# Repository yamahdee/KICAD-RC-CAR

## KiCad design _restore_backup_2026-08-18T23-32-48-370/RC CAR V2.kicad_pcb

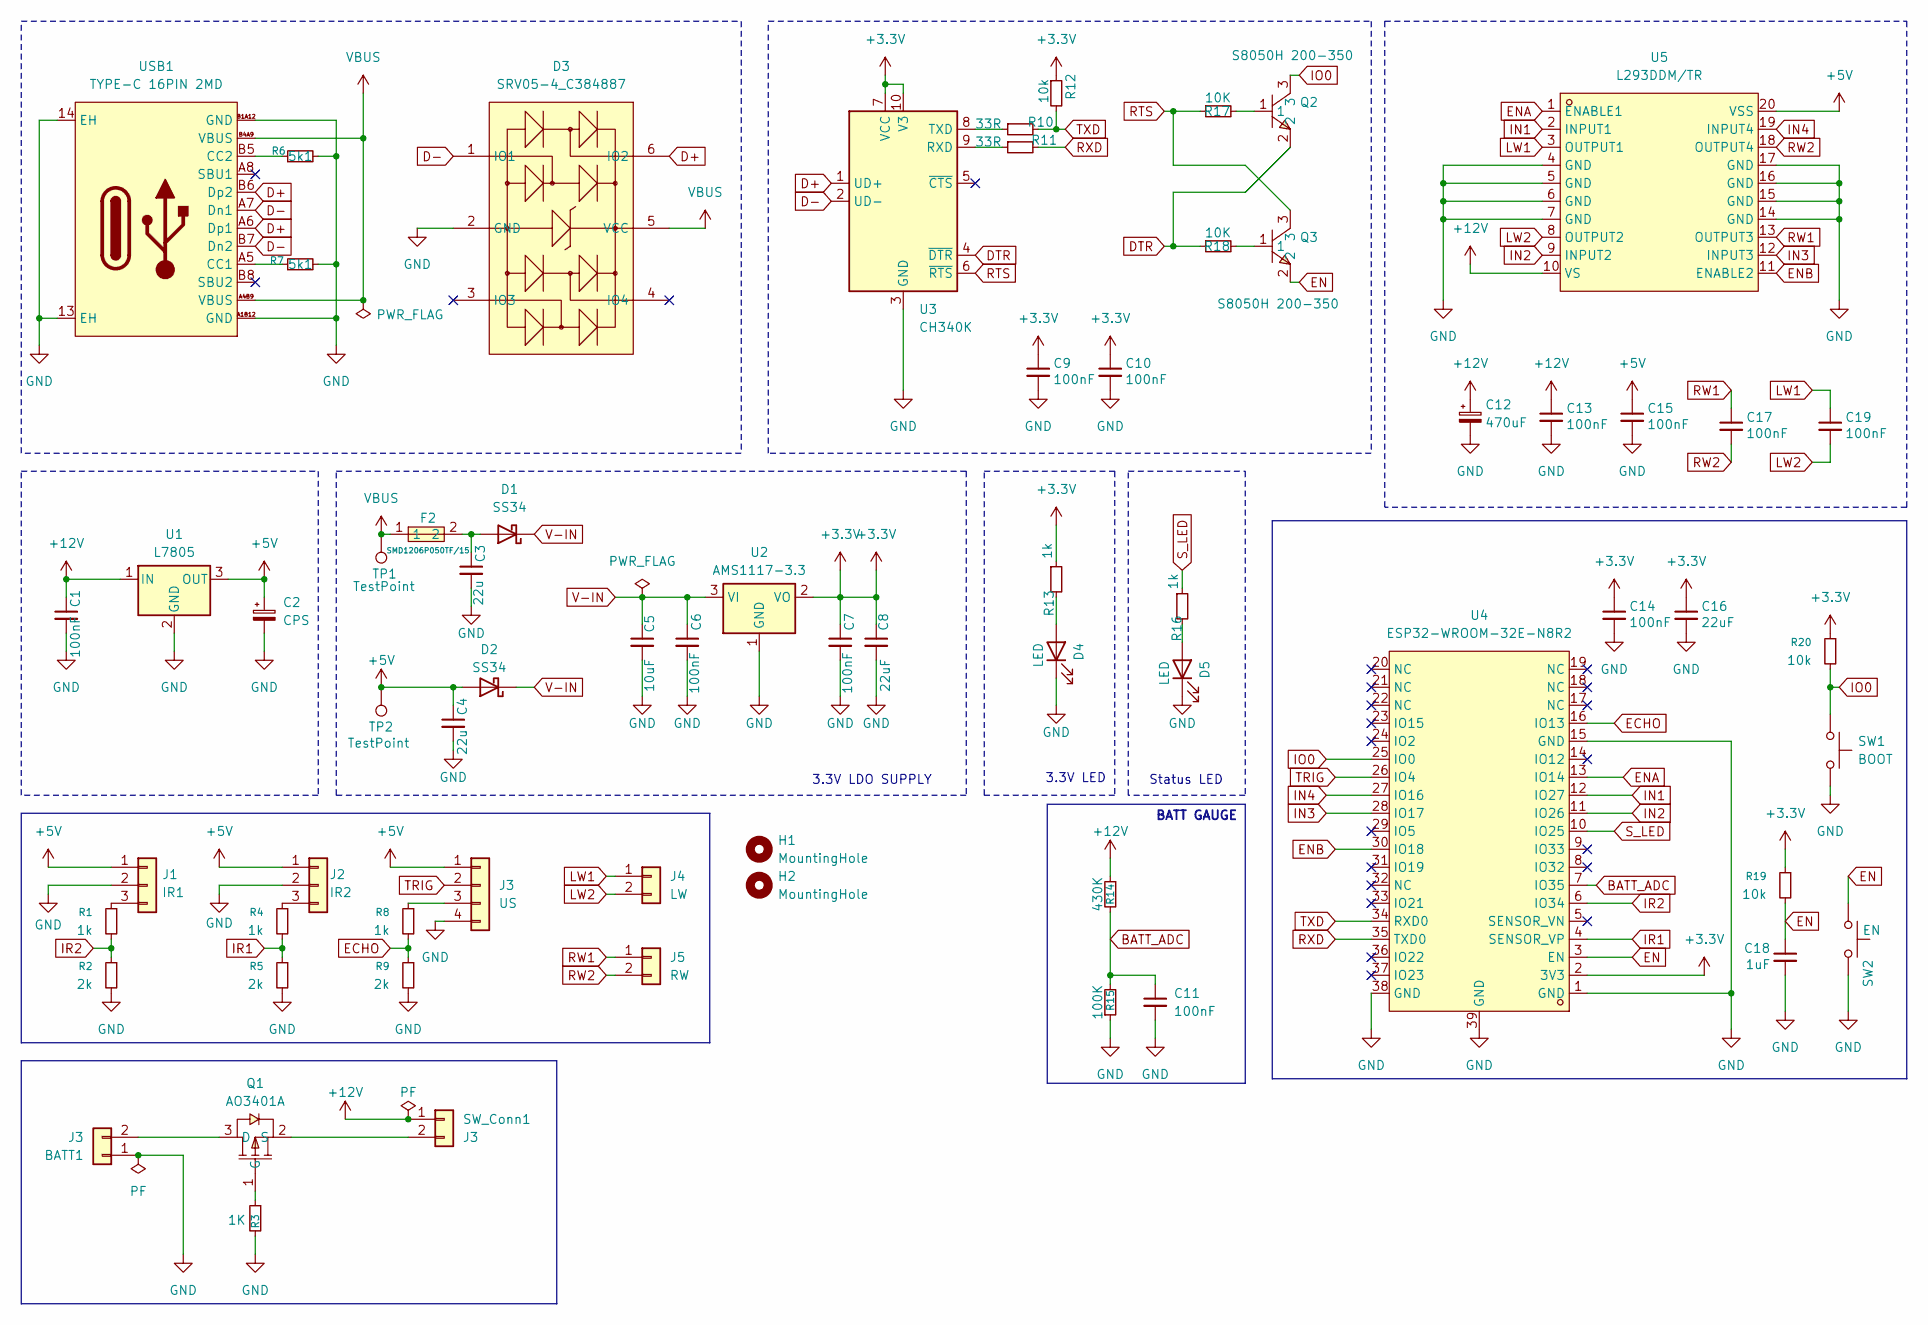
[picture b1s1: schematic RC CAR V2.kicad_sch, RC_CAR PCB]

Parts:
BATT1: J3; JST_XH_B2B-XH-AM_1x02_P2.50mm_Vertical
C1, C6, C7, C9, C10, C11, C13, C14, C15, C17, C19: 100nF; C_0805_2012Metric_Pad1.18x1.45mm_HandSolder
C2: CPS; CP_Radial_D5.0mm_P2.50mm
C3, C4: 22u; C_0805_2012Metric_Pad1.18x1.45mm_HandSolder
C5: 10uF; C_0805_2012Metric_Pad1.18x1.45mm_HandSolder
C8, C16: 22uF; C_0805_2012Metric_Pad1.18x1.45mm_HandSolder
C12: 470uF; CP_Radial_D8.0mm_P3.50mm
C18: 1uF; C_0805_2012Metric_Pad1.18x1.45mm_HandSolder
D1, D2: SS34; D_SMA_Handsoldering
D3: SRV05-4_C384887; SOT-23-6_L2.9-W1.6-P0.95-LS2.8-BR; MPN SRV05-4; LCSC Part C384887
D4, D5: LED; LED_0805_2012Metric_Pad1.15x1.40mm_HandSolder
F2: SMD1206P050TF/15; F1206; MPN SMD1206P050TF/15; LCSC Part C106264
H1, H2: MountingHole; MountingHole_2.1mm
J1: IR1; JST_XH_B3B-XH-AM_1x03_P2.50mm_Vertical
J2: IR2; JST_XH_B3B-XH-AM_1x03_P2.50mm_Vertical
J3: US; PinHeader_1x04_P2.54mm_Vertical
J4: LW; JST_XH_B2B-XH-AM_1x02_P2.50mm_Vertical
J5: RW; JST_XH_B2B-XH-AM_1x02_P2.50mm_Vertical
Q1: AO3401A; SOT-23_L2.9-W1.3-P1.90-LS2.4-BR; MPN AO3401A; LCSC Part C15127
Q2, Q3: S8050H 200-350; SOT-23-3_L2.9-W1.6-P1.90-LS2.8-BR; MPN S8050; LCSC Part C111272
R1, R4, R8, R13, R16: 1k; R_0805_2012Metric_Pad1.20x1.40mm_HandSolder
R2, R5, R9: 2k; R_0805_2012Metric_Pad1.20x1.40mm_HandSolder
R3: 1K; R_0805_2012Metric_Pad1.20x1.40mm_HandSolder
R6, R7: 5k1; R_0805_2012Metric_Pad1.20x1.40mm_HandSolder
R10, R11: 33R; R_0805_2012Metric_Pad1.20x1.40mm_HandSolder
R12, R19, R20: 10k; R_0805_2012Metric_Pad1.20x1.40mm_HandSolder
R14: 430K; R_0805_2012Metric_Pad1.20x1.40mm_HandSolder
R15: 100K; R_0805_2012Metric_Pad1.20x1.40mm_HandSolder
R17, R18: 10K; R_0805_2012Metric_Pad1.20x1.40mm_HandSolder
SW1: BOOT; SW_Tactile_SPST_NO_Straight_CK_PTS636Sx25SMTRLFS
SW2: EN; SW_Tactile_SPST_NO_Straight_CK_PTS636Sx25SMTRLFS
SW_Conn1: J3; JST_XH_B2B-XH-AM_1x02_P2.50mm_Vertical
TP1, TP2: TestPoint; TestPoint_Pad_D1.0mm
U1: L7805; TO-263-3_TabPin2
U2: AMS1117-3.3; SOT-223-3_TabPin2
U3: CH340K; SSOP-10-1EP_3.9x4.9mm_P1mm_EP2.1x3.3mm
U4: ESP32-WROOM-32E-N8R2; WIFI-SMD_ESP32-WROOM-32E; MPN ESP32-WROOM-32E-N8R2; LCSC Part C5361945
U5: L293DDM/TR; SOP-20_L12.8-W7.5-P1.27-LS10.4-BL; MPN L293DDM/TR; LCSC Part C2973803
USB1: TYPE-C 16PIN 2MD; USB-C-SMD_TYPE-C-16PIN-2MD-073; MPN TYPE-C 16PIN 2MD(073); LCSC Part C2765186

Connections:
+3.3V: C7.1, C8.1, C9.1, C10.1, C14.1, C16.1, R12.1, R13.1, R19.1, R20.1, U2.2 (VO), U3.7 (VCC), U3.10 (V3), U4.2 (3V3)
+5V: C2.1, C4.1, C15.1, D2.2 (A), J1.1, J2.1, J3.1, TP2.1 (1_1), U1.3 (OUT), U5.20 (VSS)
+12V: C1.1, C12.1, C13.1, R14.1, SW_Conn1.1, U1.1 (IN), U5.10 (VS)
BATT_ADC: C11.1, R14.2, R15.2, U4.7 (IO35)
D+: D3.6 (IO2), U3.1 (UD+), USB1.A6 (Dp1), USB1.B6 (Dp2)
D-: D3.1 (IO1), U3.2 (UD-), USB1.A7 (Dn1), USB1.B7 (Dn2)
DTR: Q2.2, R18.1, U3.4 (~DTR)
ECHO: R8.2, R9.1, U4.16 (IO13)
EN: C18.1, Q3.2, R19.2, SW2.1, U4.3 (EN)
ENA: U4.13 (IO14), U5.1 (ENABLE1)
ENB: U4.30 (IO18), U5.11 (ENABLE2)
GND: BATT1.1, C1.2, C2.2, C3.2, C4.2, C5.2, C6.2, C7.2, C8.2, C9.2, C10.2, C11.2, C12.2, C13.2, C14.2, C15.2, C16.2, C18.2, D3.2 (GND), D4.1 (K), D5.1 (K), J1.2, J2.2, J3.4, R2.2, R3.2, R5.2, R6.2, R7.2, R9.2, R15.1, SW1.2, SW2.2, U1.2 (GND), U2.1 (GND), U3.3 (GND), U3.11 (GND), U4.1 (GND), U4.15 (GND), U4.38 (GND), U4.39 (GND), U5.4 (GND), U5.5 (GND), U5.6 (GND), U5.7 (GND), U5.14 (GND), U5.15 (GND), U5.16 (GND), U5.17 (GND), USB1.13 (EH), USB1.14 (EH), USB1.A1B12 (GND), USB1.B1A12 (GND)
IN1: U4.12 (IO27), U5.2 (INPUT1)
IN2: U4.11 (IO26), U5.9 (INPUT2)
IN3: U4.28 (IO17), U5.12 (INPUT3)
IN4: U4.27 (IO16), U5.19 (INPUT4)
IO0: Q2.3, R20.2, SW1.1, U4.25 (IO0)
IR1: R4.2, R5.1, U4.4 (SENSOR_VP)
IR2: R1.2, R2.1, U4.6 (IO34)
LW1: C19.1, J4.1, U5.3 (OUTPUT1)
LW2: C19.2, J4.2, U5.8 (OUTPUT2)
unnamed: BATT1.2, Q1.3 (D)
unnamed: C3.1, D1.2 (A), F2.2
unnamed: D4.2 (A), R13.2
unnamed: D5.2 (A), R16.2
unnamed: J1.3, R1.1
unnamed: J2.3, R4.1
unnamed: J3.3, R8.1
unnamed: Q1.1 (G), R3.1
unnamed: Q1.2 (S), SW_Conn1.2
unnamed: Q2.1, R17.2
unnamed: Q3.1, R18.2
unnamed: R11.1, U3.9 (RXD)
unnamed: R10.1, U3.8 (TXD)
unnamed: R7.1, USB1.A5 (CC1)
unnamed: R6.1, USB1.B5 (CC2)
RTS: Q3.3, R17.1, U3.6 (~RTS)
RW1: C17.1, J5.1, U5.13 (OUTPUT3)
RW2: C17.2, J5.2, U5.18 (OUTPUT4)
RXD: R11.2, U4.35 (TXD0)
S_LED: R16.1, U4.10 (IO25)
TRIG: J3.2, U4.26 (IO4)
TXD: R10.2, R12.2, U4.34 (RXD0)
V-IN: C5.1, C6.1, D1.1 (K), D2.1 (K), U2.3 (VI)
VBUS: D3.5 (VCC), F2.1, TP1.1 (1_1), USB1.A4B9 (VBUS), USB1.B4A9 (VBUS)

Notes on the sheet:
3.3V LED
Status LED
3.3V LDO SUPPLY
BATT GAUGE

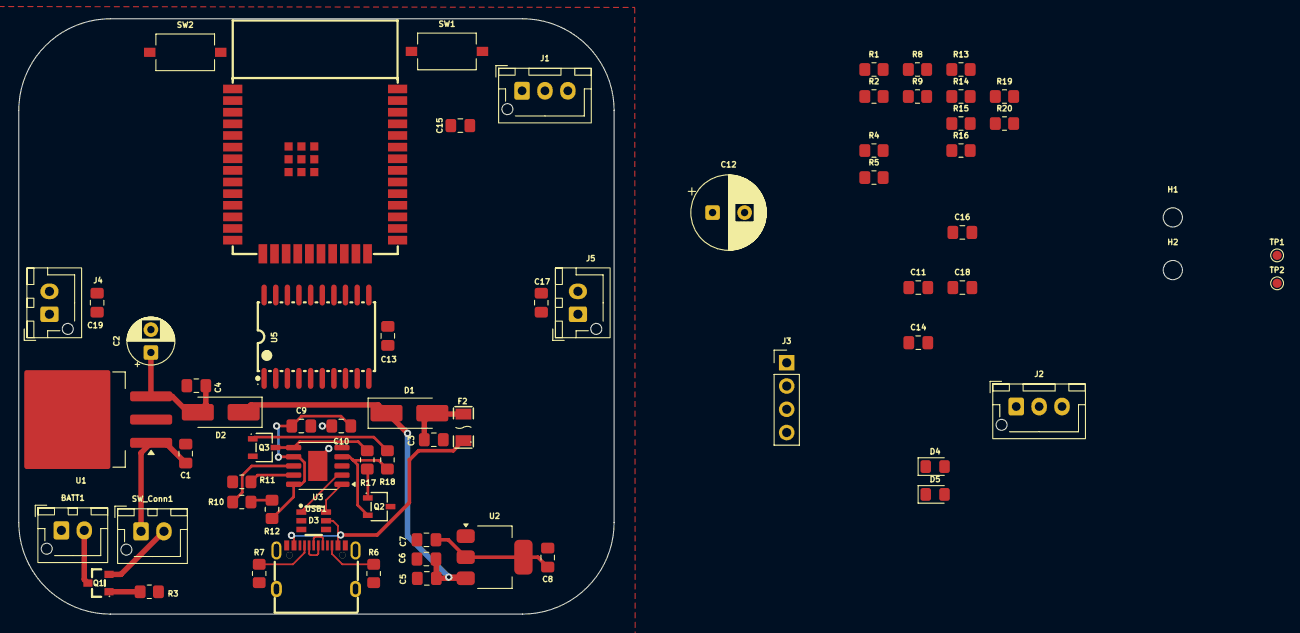
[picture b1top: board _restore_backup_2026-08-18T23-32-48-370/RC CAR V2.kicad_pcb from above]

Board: 2 copper layers, 65.0 x 65.0 mm, 67 parts (0 on the bottom side), 45 nets.

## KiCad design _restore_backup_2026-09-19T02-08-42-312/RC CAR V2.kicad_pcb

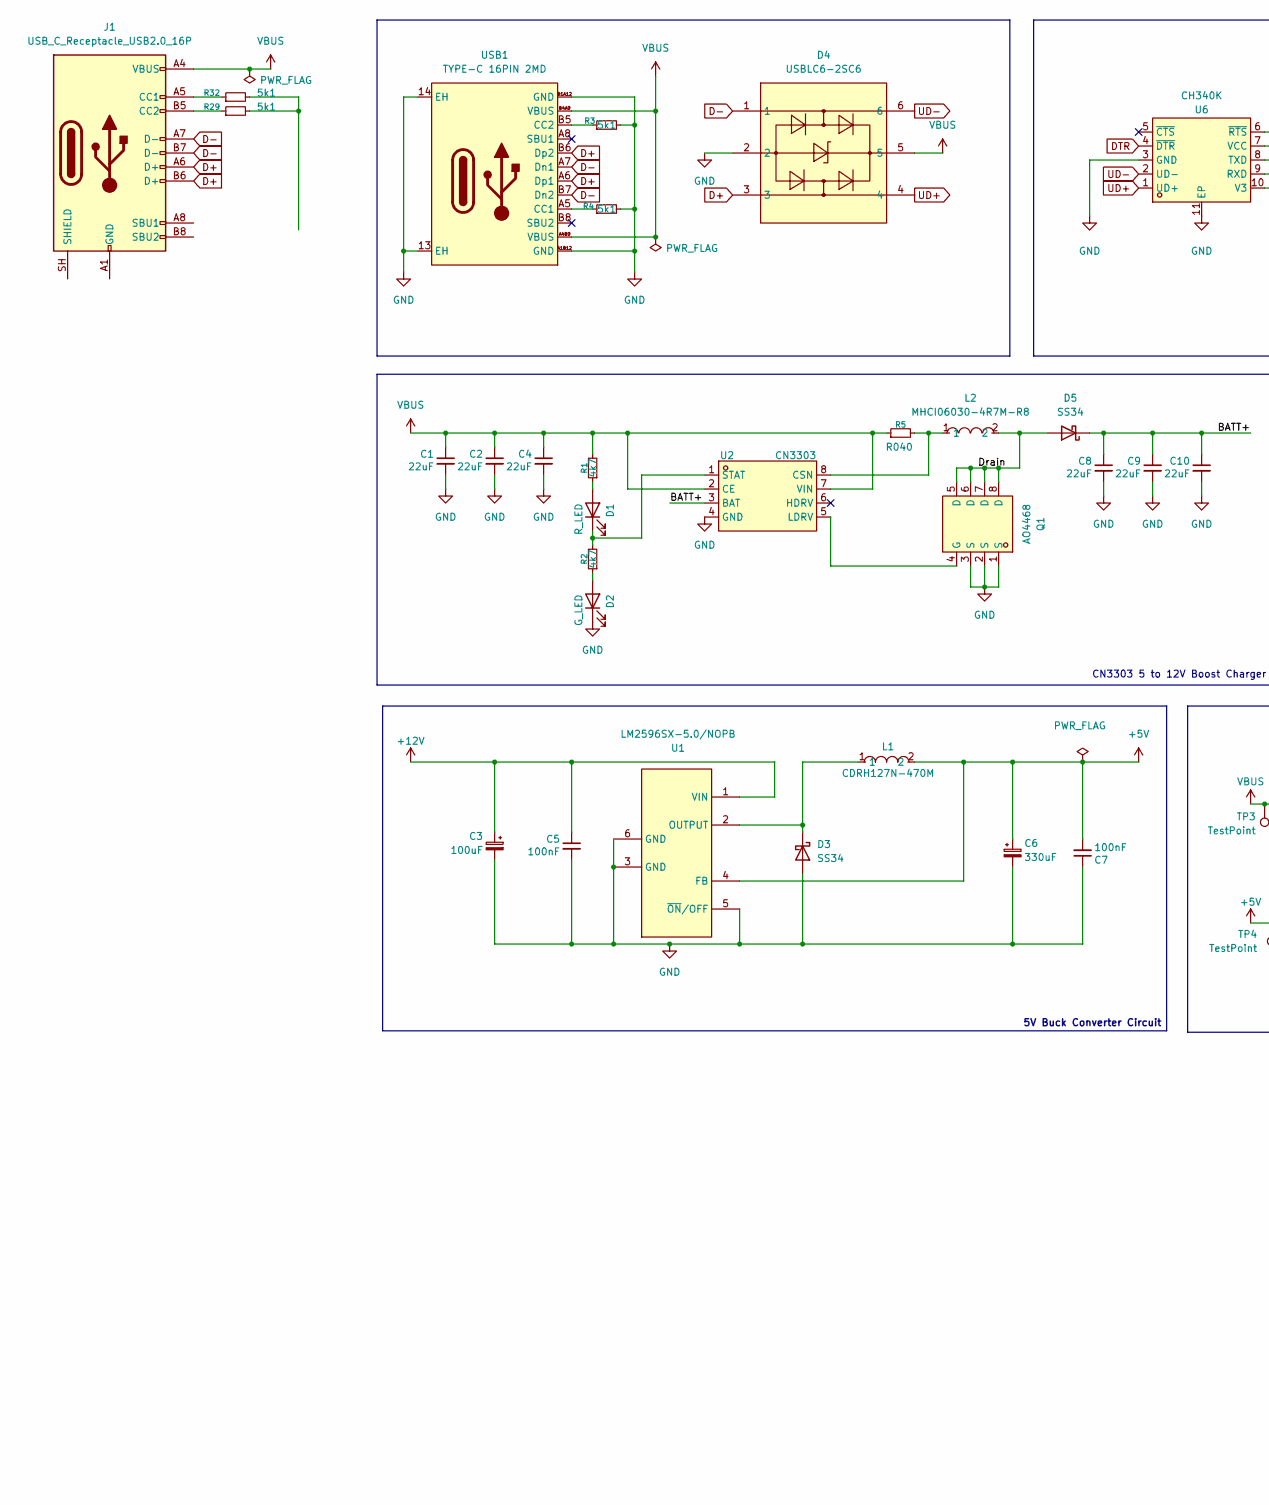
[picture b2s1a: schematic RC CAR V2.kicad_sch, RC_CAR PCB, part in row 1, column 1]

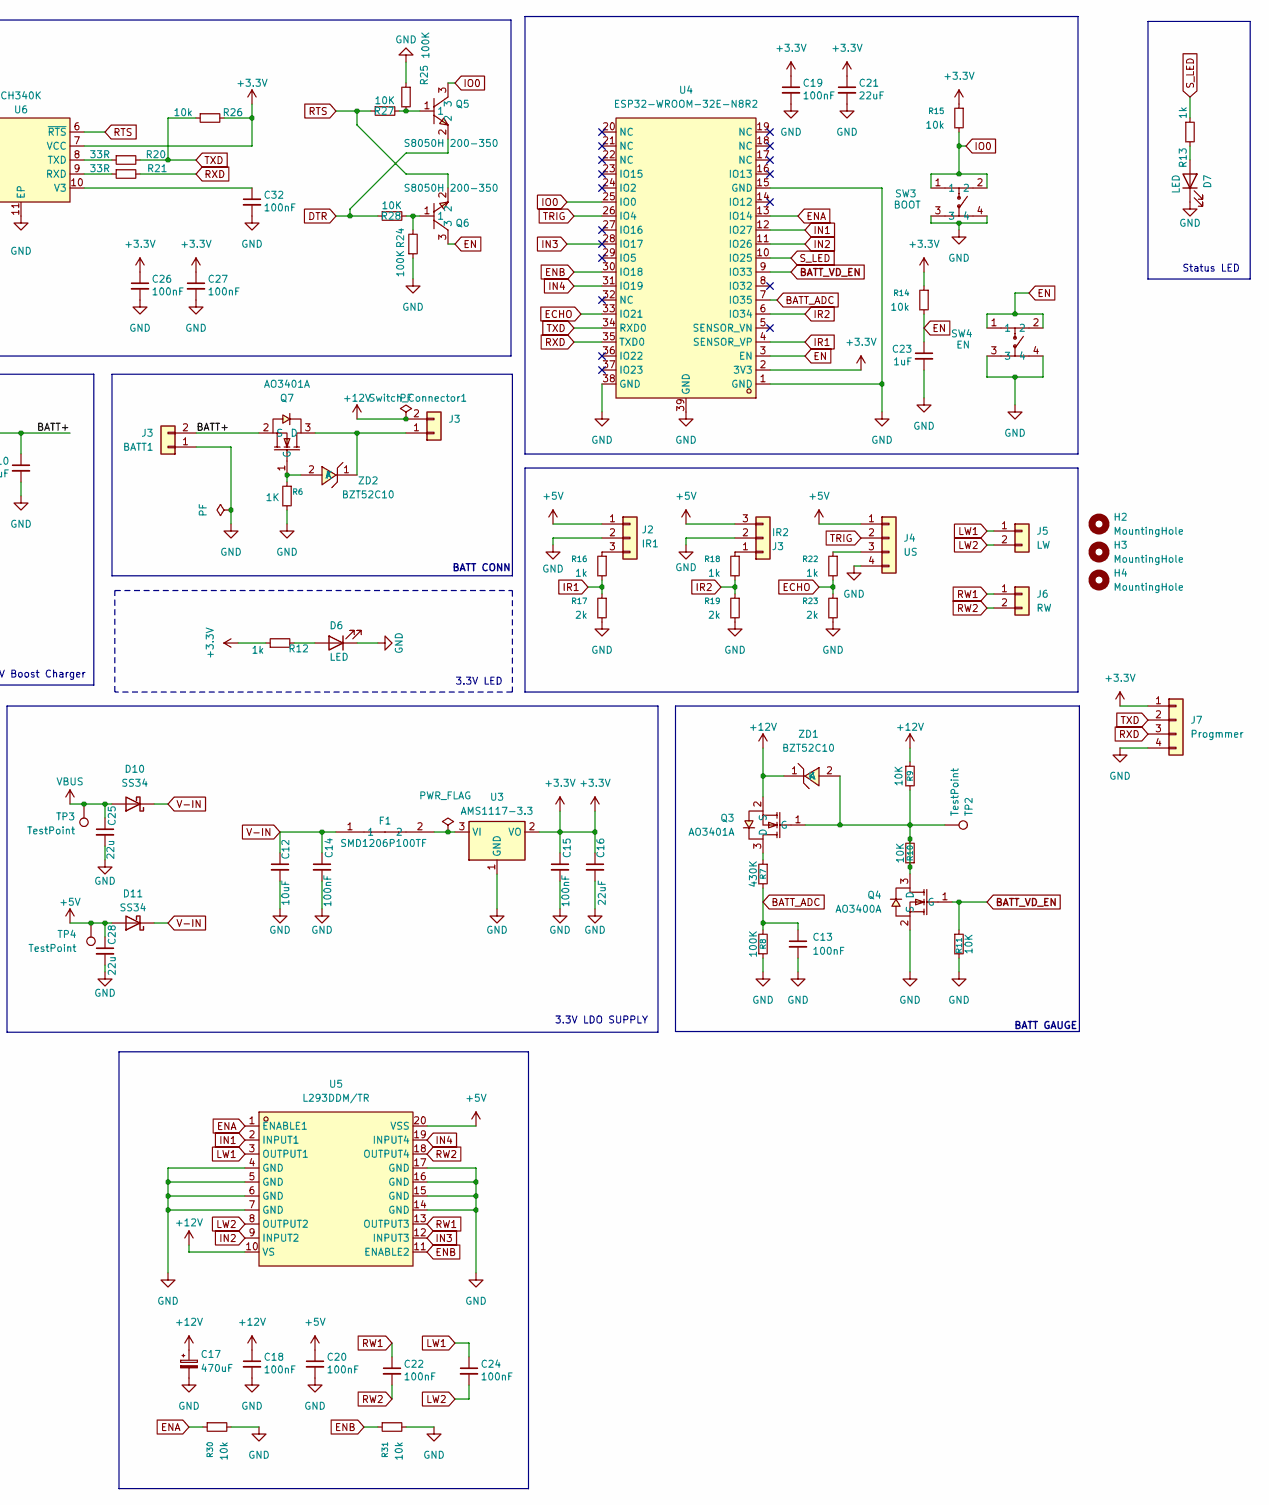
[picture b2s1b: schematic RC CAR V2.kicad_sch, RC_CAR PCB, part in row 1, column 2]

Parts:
BATT1: J3; JST_XH_B2B-XH-AM_1x02_P2.50mm_Vertical
C1, C2, C4, C8, C9, C10, C16, C21: 22uF; C_0805_2012Metric_Pad1.18x1.45mm_HandSolder
C3: 100uF; CP_Elec_8x10; LCSC Part C3352
C5, C7: 100nF; C_0805_2012Metric_Pad1.18x1.45mm_HandSolder; LCSC Part C1711
C6: 330uF; CP_Elec_10x10.5; LCSC Part C19606
C12: 10uF; C_0805_2012Metric_Pad1.18x1.45mm_HandSolder
C13, C14, C15, C18, C19, C20, C22, C24, C26, C27, C32: 100nF; C_0805_2012Metric_Pad1.18x1.45mm_HandSolder
C17: 470uF; C_Elec_10x10.2
C23: 1uF; C_0805_2012Metric_Pad1.18x1.45mm_HandSolder
C25, C28: 22u; C_0805_2012Metric_Pad1.18x1.45mm_HandSolder
D1: R_LED; LED_0805_2012Metric_Pad1.15x1.40mm_HandSolder
D2: G_LED; LED_0805_2012Metric_Pad1.15x1.40mm_HandSolder
D3, D5: SS34; D_SMA; LCSC Part C8678
D4: USBLC6-2SC6; SOT-23-6_L2.9-W1.6-P0.95-LS2.8-BL; MPN USBLC6-2SC6; LCSC Part C7519
D6, D7: LED; LED_0805_2012Metric_Pad1.15x1.40mm_HandSolder
D10, D11: SS34; D_SMA_Handsoldering
F1: SMD1206P100TF; F1206; MPN SMD1206P100TF; LCSC Part C20800
H2, H3, H4: MountingHole; MountingHole_2.1mm
J1: USB_C_Receptacle_USB2.0_16P
J2: IR1; JST_XH_B3B-XH-AM_1x03_P2.50mm_Vertical
J3: IR2; JST_XH_B3B-XH-AM_1x03_P2.50mm_Vertical
J4: US; PinHeader_1x04_P2.54mm_Vertical
J5: LW; JST_XH_B2B-XH-AM_1x02_P2.50mm_Vertical
J6: RW; JST_XH_B2B-XH-AM_1x02_P2.50mm_Vertical
J7: Progmmer; PinHeader_1x04_P2.54mm_Vertical
L1: CDRH127N-470M; IND-SMD_L12.3-W12.3; MPN CDRH127N-470M; LCSC Part C962356
L2: MHCI06030-4R7M-R8; IND-SMD_L7.3-W6.6_MHCI06030; MPN MHCI06030-4R7M-R8; LCSC Part C108295
Q1: AO4468; SOP-8_L4.9-W3.9-P1.27-LS6.0-BL; MPN AO4468; LCSC Part C87410
Q3, Q7: AO3401A; SOT-23-3_L2.9-W1.3-P1.90-LS2.4-BR; MPN AO3400A; LCSC Part C20917
Q4: AO3400A; SOT-23-3_L2.9-W1.3-P1.90-LS2.4-BR; MPN AO3400A; LCSC Part C20917
Q5, Q6: S8050H 200-350; SOT-23-3_L2.9-W1.6-P1.90-LS2.8-BR; MPN S8050; LCSC Part C111272
R1, R2: 4k7; R_0805_2012Metric_Pad1.20x1.40mm_HandSolder
R3, R4, R29, R32: 5k1; R_0805_2012Metric_Pad1.20x1.40mm_HandSolder
R5: R040; R_1206_3216Metric_Pad1.30x1.75mm_HandSolder; LCSC Part C154679
R6: 1K; R_0805_2012Metric_Pad1.20x1.40mm_HandSolder
R7: 430K; R_0805_2012Metric_Pad1.20x1.40mm_HandSolder
R8, R24, R25: 100K; R_0805_2012Metric_Pad1.20x1.40mm_HandSolder
R9, R10, R11, R27, R28: 10K; R_0805_2012Metric_Pad1.20x1.40mm_HandSolder
R12, R13, R16, R18, R22: 1k; R_0805_2012Metric_Pad1.20x1.40mm_HandSolder
R14, R15, R26, R30, R31: 10k; R_0805_2012Metric_Pad1.20x1.40mm_HandSolder
R17, R19, R23: 2k; R_0805_2012Metric_Pad1.20x1.40mm_HandSolder
R20, R21: 33R; R_0805_2012Metric_Pad1.20x1.40mm_HandSolder
SW3: BOOT; SW-SMD_4P-L4.2-W3.4-P2.15-LS5.2; MPN HX 3x4x2.5-PA-4N push button switch; LCSC Part C55200589
SW4: EN; SW-SMD_4P-L4.2-W3.4-P2.15-LS5.2; MPN HX 3x4x2.5-PA-4N push button switch; LCSC Part C55200589
Switch_Connector1: J3; JST_XH_B2B-XH-AM_1x02_P2.50mm_Vertical
TP2: TestPoint; TestPoint_Pad_1.0x1.0mm
TP3, TP4: TestPoint; TestPoint_Pad_D1.0mm
U1: LM2596SX-5.0/NOPB; TO-263-5_L10.2-W8.9-P1.70-TL; MPN LM2596SX-5.0/NOPB; LCSC Part C10002
U2: CN3303; SOP-8_L4.9-W3.9-P1.27-LS6.0-BL-1; MPN CN3303; LCSC Part C3034873
U3: AMS1117-3.3; SOT-223-3_TabPin2
U4: ESP32-WROOM-32E-N8R2; WIFI-SMD_ESP32-WROOM-32E; MPN ESP32-WROOM-32E-N8R2; LCSC Part C5361945
U5: L293DDM/TR; SOP-20_L12.8-W7.5-P1.27-LS10.4-BL; MPN L293DDM/TR; LCSC Part C2973803
U6: CH340K; ESOP-10_L4.9-W3.9-P1.00-LS6.2-BL-EP; MPN CH340K; LCSC Part C968586
USB1: TYPE-C 16PIN 2MD; USB_C_Receptacle_Palconn_UTC16-G; MPN TYPE-C 16PIN 2MD(073); LCSC Part C2765186
ZD1, ZD2: BZT52C10; SOD-123_L2.8-W1.8-LS3.7-RD; MPN BZT52C10; LCSC Part C2103

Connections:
+3.3V: C15.1, C16.1, C19.1, C21.1, C26.1, C27.1, J7.1, R12.1, R14.1, R15.1, R26.2, U3.2 (VO), U4.2 (3V3), U6.7 (VCC)
+5V: C6.1, C7.2, C20.1, C28.1, D11.2 (A), J2.1, J3.3, J4.1, L1.2, TP4.1 (1_1), U1.4 (FB), U5.20 (VSS); also elsewhere on the board
+12V: C3.1, C5.1, C17.1, C18.1, Q3.2 (S), R9.1, Switch_Connector1.2, U1.1 (VIN), U5.10 (VS), ZD1.1 (K)
/BATT+: BATT1.2, C8.1, C9.1, C10.1, D5.1 (K), Q7.2 (S), U2.3 (BAT)
/Drain: D5.2 (A), L2.2, Q1.5 (D), Q1.6 (D), Q1.7 (D), Q1.8 (D)
BATT_ADC: C13.1, R7.2, R8.2, U4.7 (IO35)
BATT_VD_EN: Q4.1 (G), R11.1, U4.9 (IO33)
D+: D4.3, J1.A6 (D+), J1.B6 (D+), USB1.A6 (Dp1), USB1.B6 (Dp2)
D-: D4.1, J1.A7 (D-), J1.B7 (D-), USB1.A7 (Dn1), USB1.B7 (Dn2)
DTR: Q5.2, R28.1, U6.4 (~DTR)
ECHO: R22.2, R23.1, U4.33 (IO21)
EN: C23.1, Q6.3, R14.2, SW4.1, SW4.2, U4.3 (EN)
ENA: R30.1, U4.13 (IO14), U5.1 (ENABLE1)
ENB: R31.1, U4.30 (IO18), U5.11 (ENABLE2)
GND: BATT1.1, C1.2, C2.2, C3.2, C4.2, C5.2, C6.2, C7.1, C8.2, C9.2, C10.2, C12.2, C13.2, C14.2, C15.2, C16.2, C17.2, C18.2, C19.2, C20.2, C21.2, C23.2, C25.2, C26.2, C27.2, C28.2, C32.2, D2.1 (K), D3.2 (A), D4.2, D6.1 (K), D7.1 (K), J2.2, J3.2, J4.4, J7.4, Q1.1 (S), Q1.2 (S), Q1.3 (S), Q4.2 (S), R3.2, R4.2, R6.2, R8.1, R11.2, R17.2, R19.2, R23.2, R24.1, R25.1, R30.2, R31.2, SW3.3, SW3.4, SW4.3, SW4.4, U1.3 (GND), U1.5 (~ON/OFF), U1.6 (GND), U2.4 (GND), U3.1 (GND), U4.1 (GND), U4.15 (GND), U4.38 (GND), U4.39 (GND), U5.4 (GND), U5.5 (GND), U5.6 (GND), U5.7 (GND), U5.14 (GND), U5.15 (GND), U5.16 (GND), U5.17 (GND), U6.3 (GND), U6.11 (EP), USB1.13 (EH), USB1.14 (EH), USB1.A1B12 (GND), USB1.B1A12 (GND); also elsewhere on the board
IN1: U4.12 (IO27), U5.2 (INPUT1)
IN2: U4.11 (IO26), U5.9 (INPUT2)
IN3: U4.28 (IO17), U5.12 (INPUT3)
IN4: U4.31 (IO19), U5.19 (INPUT4)
IO0: Q5.3, R15.2, SW3.1, SW3.2, U4.25 (IO0)
IR1: R16.2, R17.1, U4.4 (SENSOR_VP)
IR2: R18.2, R19.1, U4.6 (IO34)
LW1: C24.1, J5.1, U5.3 (OUTPUT1)
LW2: C24.2, J5.2, U5.8 (OUTPUT2)
unnamed: D1.2 (A), R1.1
unnamed: D1.1 (K), R2.2, U2.1 (STAT)
unnamed: D2.2 (A), R2.1
unnamed: D3.1 (K), L1.1, U1.2 (OUTPUT)
unnamed: D6.2 (A), R12.2
unnamed: D7.2 (A), R13.2
unnamed: J1.A1 (GND), J1.A12 (GND), J1.B1 (GND), J1.B12 (GND)
unnamed: J1.A5 (CC1), R32.1
unnamed: J1.B5 (CC2), R29.1
unnamed: J2.3, R16.1
unnamed: J3.1, R18.1
unnamed: J4.3, R22.1
unnamed: Q1.4 (G), U2.5 (LDRV)
unnamed: Q3.3 (D), R7.1
unnamed: Q3.1 (G), Q4.3 (D), R9.2, R10.1, R10.2, TP2.1 (1_1), ZD1.2 (A)
unnamed: Q5.1, R25.2, R27.2
unnamed: Q6.1, R24.2, R28.2
unnamed: Q7.3 (D), Switch_Connector1.1, ZD2.1 (K)
unnamed: Q7.1 (G), R6.1, ZD2.2 (A)
unnamed: R29.2, R32.2
unnamed: L2.1, R5.2, U2.8 (CSN)
unnamed: F1.2, U3.3 (VI)
unnamed: R21.1, U6.9 (RXD)
unnamed: R20.1, U6.8 (TXD)
unnamed: C32.1, U6.10 (V3)
unnamed: R4.1, USB1.A5 (CC1)
unnamed: R3.1, USB1.B5 (CC2)
RTS: Q6.2, R27.1, U6.6 (~RTS)
RW1: C22.1, J6.1, U5.13 (OUTPUT3)
RW2: C22.2, J6.2, U5.18 (OUTPUT4)
RXD: J7.3, R21.2, U4.35 (TXD0)
S_LED: R13.1, U4.10 (IO25)
TRIG: J4.2, U4.26 (IO4)
TXD: J7.2, R20.2, R26.1, U4.34 (RXD0)
UD+: D4.4, U6.1 (UD+)
UD-: D4.6, U6.2 (UD-)
V-IN: C12.1, C14.1, D10.1 (K), D11.1 (K), F1.1
VBUS: C1.1, C2.1, C4.1, C25.1, D4.5, D10.2 (A), J1.A4 (VBUS), J1.A9 (VBUS), J1.B4 (VBUS), J1.B9 (VBUS), R1.2, R5.1, TP3.1 (1_1), U2.2 (CE), U2.7 (VIN), USB1.A4B9 (VBUS), USB1.B4A9 (VBUS)

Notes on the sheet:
CN3303 5 to 12V Boost Charger
3.3V LED
Status LED
BATT CONN
3.3V LDO SUPPLY
5V Buck Converter Circuit
BATT GAUGE

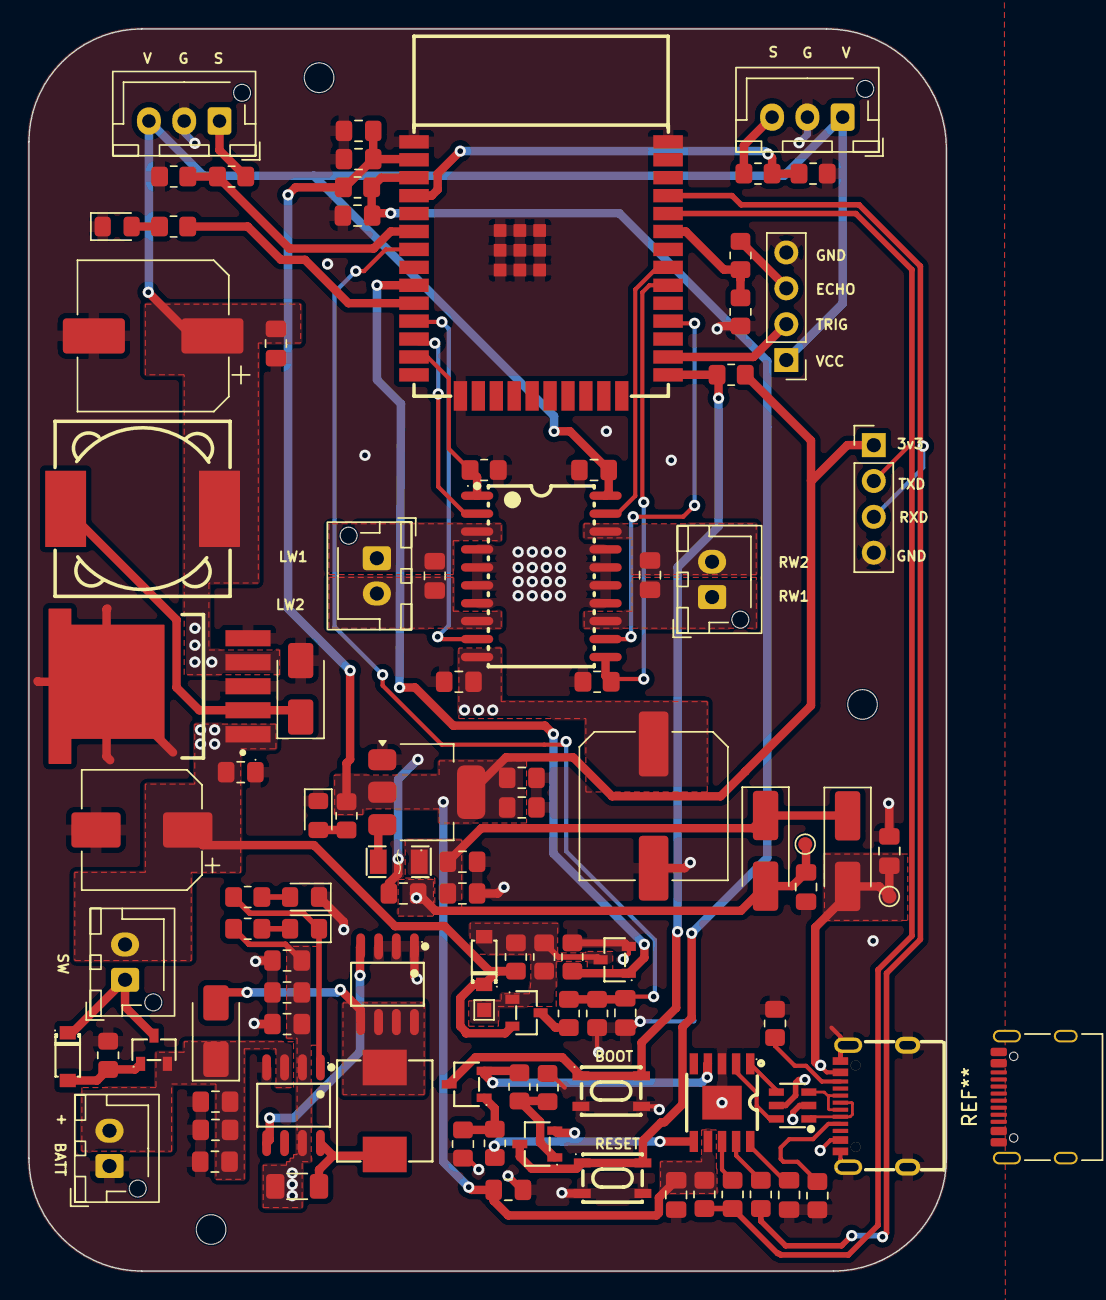
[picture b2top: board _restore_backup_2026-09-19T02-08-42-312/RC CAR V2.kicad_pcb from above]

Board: 2 copper layers, 65.0 x 88.0 mm, 103 parts (0 on the bottom side), 58 nets.

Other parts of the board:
C11: 22u; C_0805_2012Metric_Pad1.18x1.45mm_HandSolder
H1: MountingHole; MountingHole_2.1mm

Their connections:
+5V: C11.1; also elsewhere on the board
GND: C11.2; also elsewhere on the board

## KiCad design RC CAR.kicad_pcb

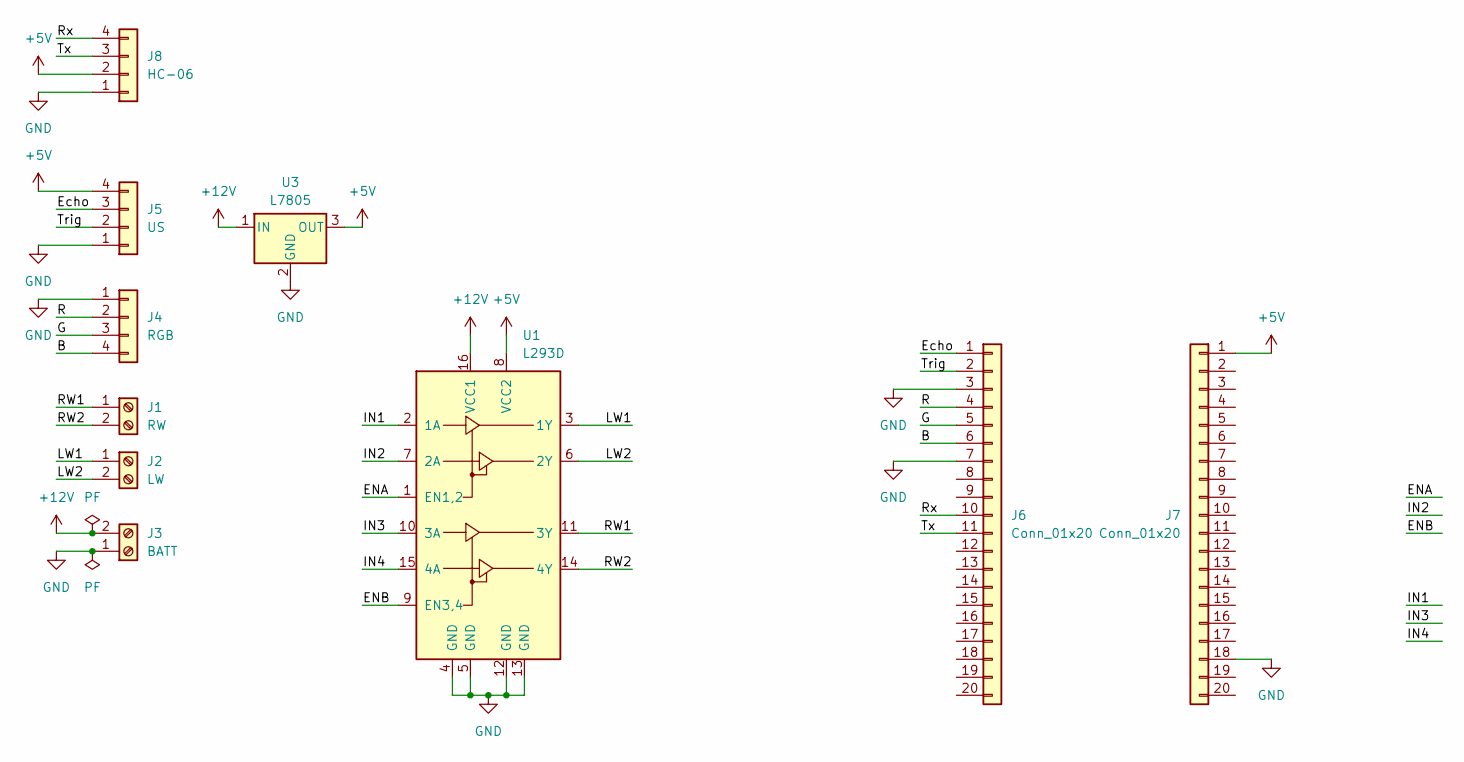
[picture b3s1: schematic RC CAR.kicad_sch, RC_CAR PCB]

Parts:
J1: RW; TerminalBlock_4Ucon_1x02_P3.50mm_Horizontal
J2: LW; TerminalBlock_4Ucon_1x02_P3.50mm_Horizontal
J3: BATT; TerminalBlock_4Ucon_1x02_P3.50mm_Horizontal
J4: RGB; PinHeader_1x04_P2.54mm_Vertical
J5: US; PinHeader_1x04_P2.54mm_Vertical
J6, J7: Conn_01x20; PinHeader_1x20_P2.54mm_Vertical
J8: HC-06; PinSocket_1x04_P2.54mm_Horizontal
U1: L293D; DIP-16_W7.62mm_Socket_LongPads
U3: L7805; TO-220-3_Vertical

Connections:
+5V: J5.4, J7.1, J8.2, U1.8 (VCC2), U3.3 (OUT)
+12V: J3.2, U1.16 (VCC1), U3.1 (IN)
/B: J4.4, J6.6
/ENA: U1.1 (EN1,2)
/ENB: U1.9 (EN3,4)
/Echo: J5.3, J6.1
/G: J4.3, J6.5
/IN1: U1.2 (1A)
/IN2: U1.7 (2A)
/IN3: U1.10 (3A)
/IN4: U1.15 (4A)
/LW1: J2.1, U1.3 (1Y)
/LW2: J2.2, U1.6 (2Y)
/R: J4.2, J6.4
/RW1: J1.1, U1.11 (3Y)
/RW2: J1.2, U1.14 (4Y)
/Rx: J6.10, J8.4
/Trig: J5.2, J6.2
/Tx: J6.11, J8.3
GND: J3.1, J4.1, J5.1, J6.3, J6.7, J7.18, J8.1, U1.4 (GND), U1.5 (GND), U1.12 (GND), U1.13 (GND), U3.2 (GND)

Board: 2 copper layers, 10 parts (0 on the bottom side), 14 nets, no tracks yet.

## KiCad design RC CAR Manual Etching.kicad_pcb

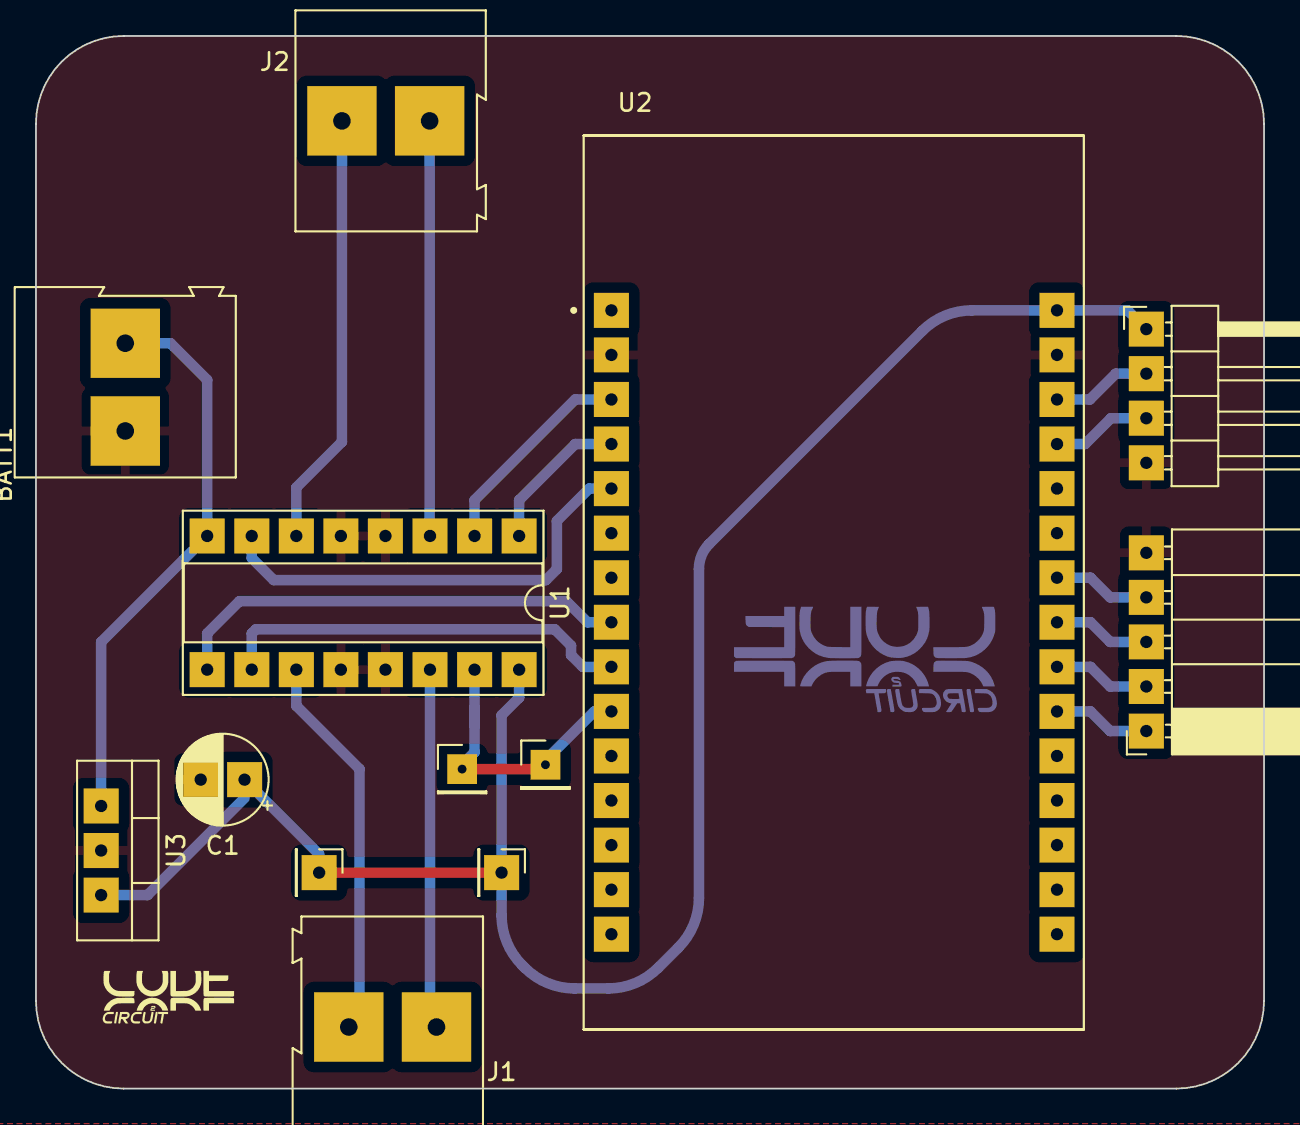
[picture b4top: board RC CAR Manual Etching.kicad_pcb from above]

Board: 2 copper layers, 70.0 x 60.0 mm, 11 parts (0 on the bottom side), 19 nets.

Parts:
BATT1: J3; TerminalBlock_Altech_AK300-2_P5.00mm
C1: CPS; CP_Radial_D5.0mm_P2.50mm
J1: RW; TerminalBlock_Altech_AK300-2_P5.00mm
J2: LW; TerminalBlock_Altech_AK300-2_P5.00mm
J4: US; PinHeader_1x04_P2.54mm_Horizontal
J5: RGB; PinSocket_1x05_P2.54mm_Horizontal
J6, J7: J2; PinHeader_1x01_P2.54mm_Vertical
U1: L293D; DIP-16_W7.62mm_Socket_LongPads
U2: ESP32-DEVKIT-V1; MODULE_ESP32_DEVKIT_V1
U3: L7805; TO-220-3_Vertical

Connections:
+5V: C1.1, J4.1, J6.1, J7.1, U1.16 (VCC1), U2.30 (VIN), U3.3 (OUT)
+12V: BATT1.2, U1.8 (VCC2), U3.1 (IN)
B: J5.2, U2.22 (D33)
ECHO: J4.2, U2.28 (D13)
ENA: U1.1 (EN1,2), U2.4 (D2)
ENB: U1.9 (EN3,4), U2.8 (D5)
G: J5.3, U2.23 (D25)
GND: BATT1.1, C1.2, J4.4, J5.5, U1.4 (GND), U1.5 (GND), U1.12 (GND), U1.13 (GND), U2.2 (GND), U2.29 (GND), U3.2 (GND)
IN1: U1.2 (1A), U2.3 (D15)
IN2: U1.7 (2A), U2.5 (D4)
IN3: U1.10 (3A), U2.9 (D18)
IN4: U1.15 (4A), U2.10 (D19)
L: J5.1, U2.21 (D32)
LW1: J2.1, U1.6 (2Y)
LW2: J2.2, U1.3 (1Y)
R: J5.4, U2.24 (D26)
RW1: J1.1, U1.14 (4Y)
RW2: J1.2, U1.11 (3Y)
TRIG: J4.3, U2.27 (D12)
